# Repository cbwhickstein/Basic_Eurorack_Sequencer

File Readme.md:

# Eurorack CD4017 10-Steps Sequencer
This Repo containes a simple 10 Step sequencer for the Eurorack Modular standard.

## Schematic

## PCB

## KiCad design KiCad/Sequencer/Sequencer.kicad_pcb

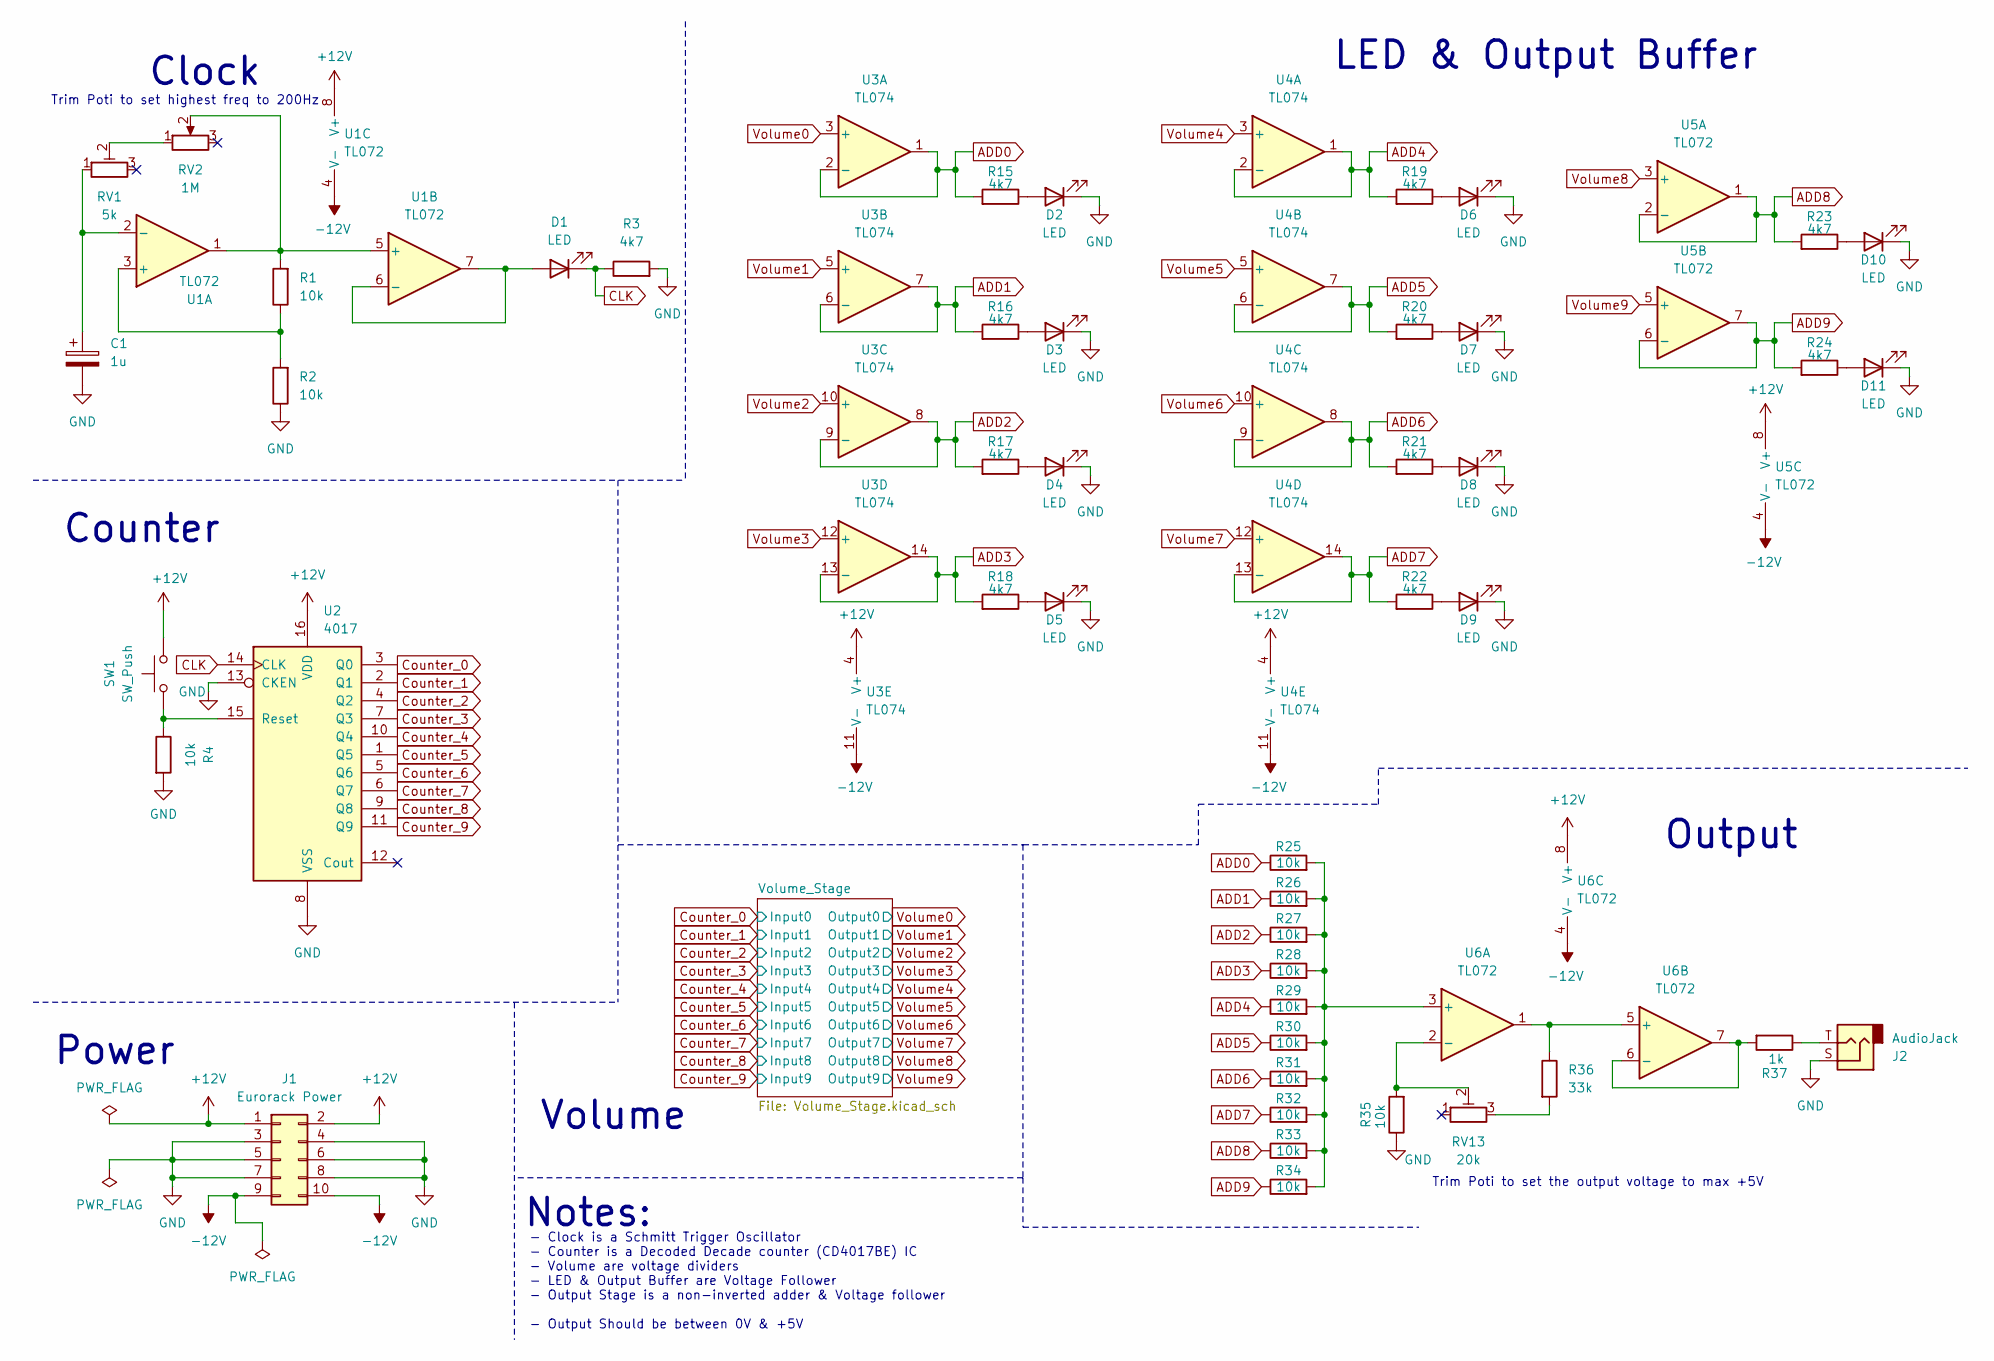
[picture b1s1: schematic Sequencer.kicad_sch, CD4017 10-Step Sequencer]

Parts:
C1: 1u; C_0805_2012Metric_Pad1.18x1.45mm_HandSolder
D1, D2, D3, D4, D5, D6, D7, D8, D9, D10, D11: LED; D_DO-34_SOD68_P2.54mm_Vertical_AnodeUp
J1: Eurorack Power; PinHeader_2x05_P2.54mm_Vertical
J2: AudioJack; Jack_3.5mm_QingPu_WQP-PJ398SM_Vertical_CircularHoles
R1, R2, R4, R25, R26, R27, R28, R29, R30, R31, R32, R33, R34, R35: 10k; R_0805_2012Metric_Pad1.20x1.40mm_HandSolder
R3, R15, R16, R17, R18, R19, R20, R21, R22, R23, R24: 4k7; R_0805_2012Metric_Pad1.20x1.40mm_HandSolder
R36: 33k; R_0805_2012Metric_Pad1.20x1.40mm_HandSolder
R37: 1k; R_0805_2012Metric_Pad1.20x1.40mm_HandSolder
RV1: 5k; Potentiometer_Piher_PT-6-V_Vertical
RV2: 1M; Potis
RV13: 20k; Potentiometer_Piher_PT-6-V_Vertical
SW1: SW_Push; SW_PUSH_1P1T_6x3.5mm_H4.3_APEM_MJTP1243
U1, U5, U6: TL072; DIP-8_W7.62mm
U2: 4017; DIP-16_W7.62mm
U3, U4: TL074; DIP-14_W7.62mm

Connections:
+12V: J1.1, J1.2, SW1.1, U1.8 (V+), U2.16 (VDD), U3.4 (V+), U4.4 (V+), U5.8 (V+), U6.8 (V+)
-12V: J1.9, J1.10, U1.4 (V-), U3.11 (V-), U4.11 (V-), U5.4 (V-), U6.4 (V-)
ADD0: R15.2, R25.1, U3.1, U3.2 (-)
ADD1: R16.2, R26.1, U3.6 (-), U3.7
ADD2: R17.2, R27.1, U3.8, U3.9 (-)
ADD3: R18.2, R28.1, U3.13 (-), U3.14
ADD4: R19.2, R29.1, U4.1, U4.2 (-)
ADD5: R20.2, R30.1, U4.6 (-), U4.7
ADD6: R21.2, R31.1, U4.8, U4.9 (-)
ADD7: R22.2, R32.1, U4.13 (-), U4.14
ADD8: R23.2, R33.1, U5.1, U5.2 (-)
ADD9: R24.2, R34.1, U5.6 (-), U5.7
CLK: D1.1 (K), R3.1, U2.14 (CLK)
Counter_0: U2.3 (Q0); also elsewhere on the board
Counter_1: U2.2 (Q1); also elsewhere on the board
Counter_2: U2.4 (Q2); also elsewhere on the board
Counter_3: U2.7 (Q3); also elsewhere on the board
Counter_4: U2.10 (Q4); also elsewhere on the board
Counter_5: U2.1 (Q5); also elsewhere on the board
Counter_6: U2.5 (Q6); also elsewhere on the board
Counter_7: U2.6 (Q7); also elsewhere on the board
Counter_8: U2.9 (Q8); also elsewhere on the board
Counter_9: U2.11 (Q9); also elsewhere on the board
GND: C1.2, D2.1 (K), D3.1 (K), D4.1 (K), D5.1 (K), D6.1 (K), D7.1 (K), D8.1 (K), D9.1 (K), D10.1 (K), D11.1 (K), J1.3, J1.4, J1.5, J1.6, J1.7, J1.8, J2.S, R2.1, R3.2, R4.2, R35.1, U2.8 (VSS), U2.13 (CKEN); also elsewhere on the board
unnamed: D1.2 (A), U1.6 (-), U1.7
unnamed: D2.2 (A), R15.1
unnamed: D3.2 (A), R16.1
unnamed: D4.2 (A), R17.1
unnamed: D5.2 (A), R18.1
unnamed: D6.2 (A), R19.1
unnamed: D7.2 (A), R20.1
unnamed: D8.2 (A), R21.1
unnamed: D9.2 (A), R22.1
unnamed: D10.2 (A), R23.1
unnamed: D11.2 (A), R24.1
unnamed: J2.T, R37.1
unnamed: R36.2, RV13.3
unnamed: RV1.2, RV2.1
unnamed: R1.1, R2.2, U1.3 (+)
unnamed: C1.1, RV1.1, U1.2 (-)
unnamed: R1.2, RV2.2, U1.1, U1.5 (+)
unnamed: R4.1, SW1.2, U2.15 (Reset)
unnamed: R25.2, R26.2, R27.2, R28.2, R29.2, R30.2, R31.2, R32.2, R33.2, R34.2, U6.3 (+)
unnamed: R35.2, RV13.2, U6.2 (-)
unnamed: R36.1, U6.1, U6.5 (+)
unnamed: R37.2, U6.6 (-), U6.7
Volume0: U3.3 (+); also elsewhere on the board
Volume1: U3.5 (+); also elsewhere on the board
Volume2: U3.10 (+); also elsewhere on the board
Volume3: U3.12 (+); also elsewhere on the board
Volume4: U4.3 (+); also elsewhere on the board
Volume5: U4.5 (+); also elsewhere on the board
Volume6: U4.10 (+); also elsewhere on the board
Volume7: U4.12 (+); also elsewhere on the board
Volume8: U5.3 (+); also elsewhere on the board
Volume9: U5.5 (+); also elsewhere on the board

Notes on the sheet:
Volume
Clock
Notes:
LED & Output Buffer
Counter
Trim Poti to set highest freq to 200Hz
- Clock is a Schmitt Trigger Oscillator - Counter is a Decoded Decade counter (CD4017BE) IC - Volume are voltage dividers - LED & Output Buffer are Voltage Follower - Output Stage is a non-inverted adder & Voltage follower - Output Should be between 0V & +5V
Power
Output
Trim Poti to set the output voltage to max +5V

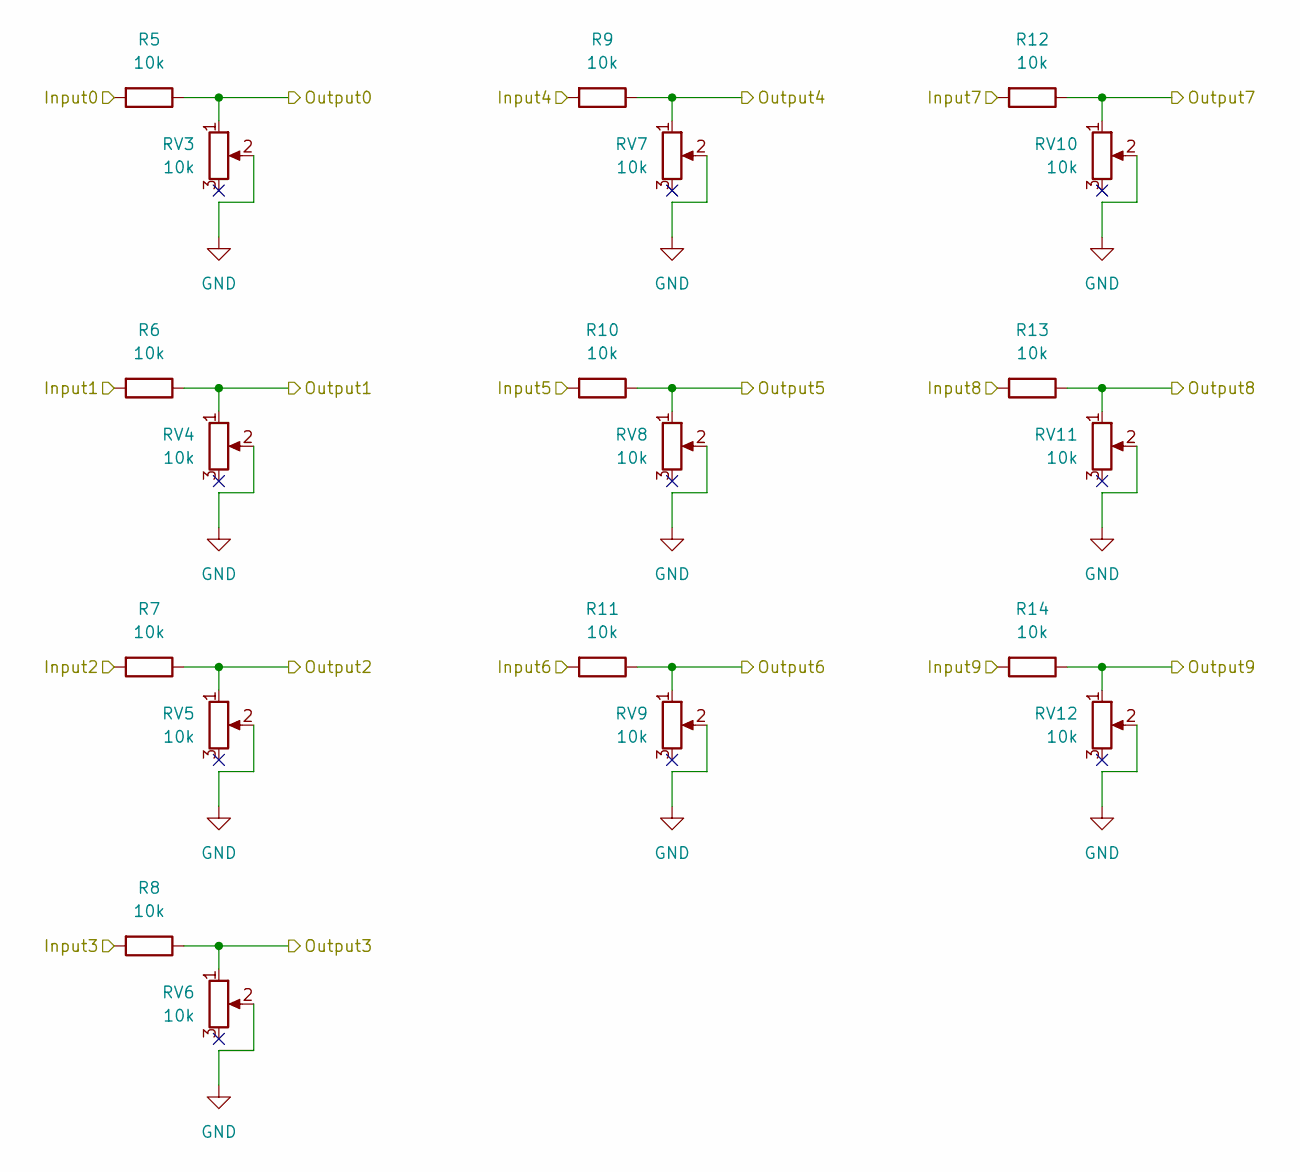
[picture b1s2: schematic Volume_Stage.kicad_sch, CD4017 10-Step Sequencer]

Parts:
R5, R6, R7, R8, R9, R10, R11, R12, R13, R14: 10k; R_0805_2012Metric_Pad1.20x1.40mm_HandSolder
RV3, RV4, RV5, RV6, RV7, RV8, RV9, RV10, RV11, RV12: 10k; Potis

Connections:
Counter_0: R5.2; also elsewhere on the board
Counter_1: R6.2; also elsewhere on the board
Counter_2: R7.2; also elsewhere on the board
Counter_3: R8.2; also elsewhere on the board
Counter_4: R9.2; also elsewhere on the board
Counter_5: R10.2; also elsewhere on the board
Counter_6: R11.2; also elsewhere on the board
Counter_7: R12.2; also elsewhere on the board
Counter_8: R13.2; also elsewhere on the board
Counter_9: R14.2; also elsewhere on the board
GND: RV3.2, RV4.2, RV5.2, RV6.2, RV7.2, RV8.2, RV9.2, RV10.2, RV11.2, RV12.2; also elsewhere on the board
Volume0: R5.1, RV3.1; also elsewhere on the board
Volume1: R6.1, RV4.1; also elsewhere on the board
Volume2: R7.1, RV5.1; also elsewhere on the board
Volume3: R8.1, RV6.1; also elsewhere on the board
Volume4: R9.1, RV7.1; also elsewhere on the board
Volume5: R10.1, RV8.1; also elsewhere on the board
Volume6: R11.1, RV9.1; also elsewhere on the board
Volume7: R12.1, RV10.1; also elsewhere on the board
Volume8: R13.1, RV11.1; also elsewhere on the board
Volume9: R14.1, RV12.1; also elsewhere on the board

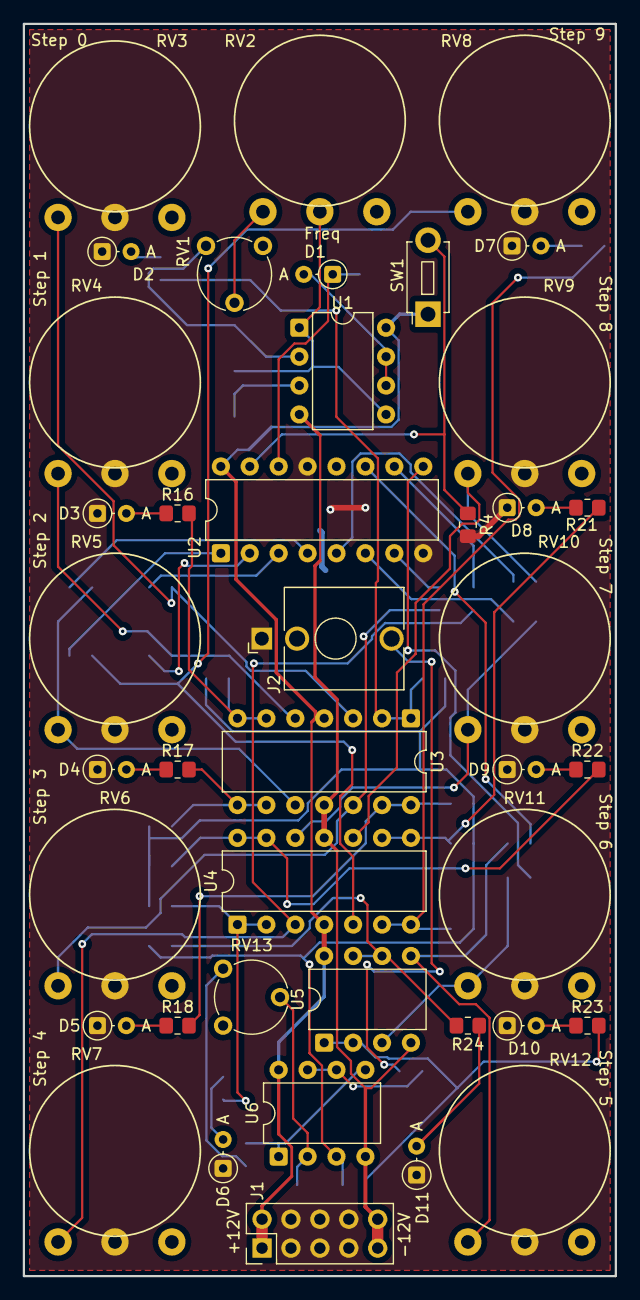
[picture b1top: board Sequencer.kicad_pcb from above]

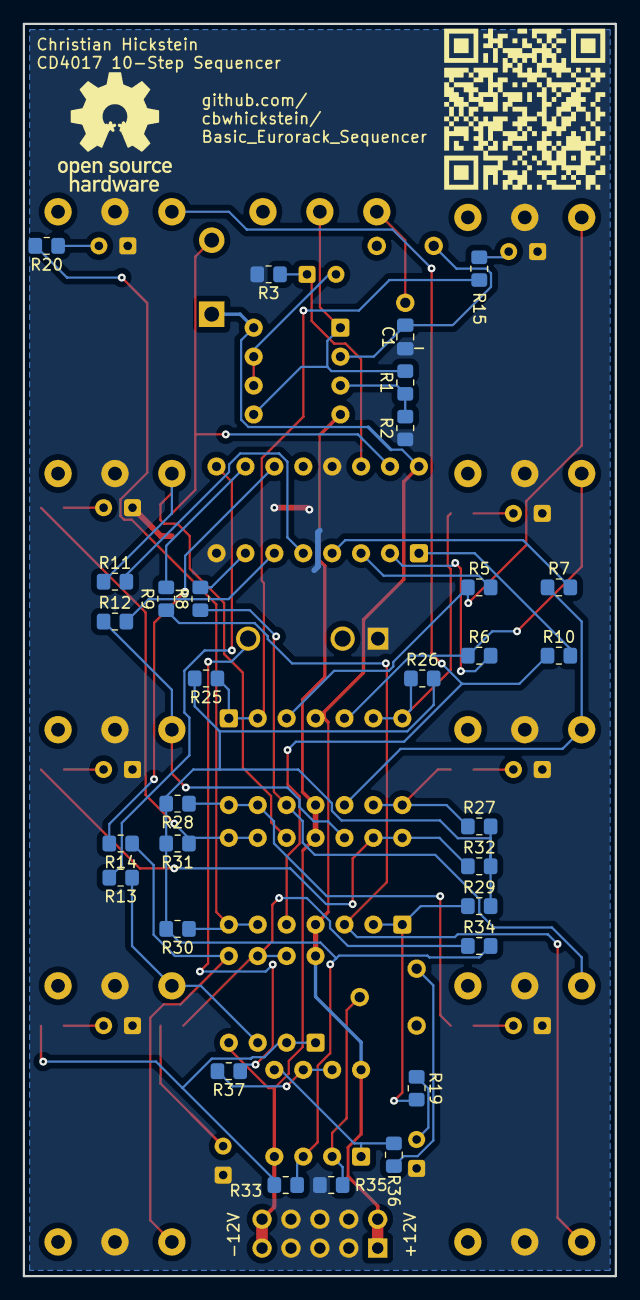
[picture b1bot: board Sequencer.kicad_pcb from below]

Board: 2 copper layers, 52.0 x 110.0 mm, 71 parts (30 on the bottom side), 56 nets.

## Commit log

2026-03-06 Finished Sequencer Schematic
2026-03-16 V1.0 Schematic Finished
2026-03-23 Finished Version 1.0 of PCB
2026-03-23 updated Readme and added License
2026-04-07 Version 1.0: Schematic Finished
